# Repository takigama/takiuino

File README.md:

# Takiuino - the arduino compatible board for ME!

Just a WIP atm, look in the eagle directory and you can see the boards and their OSHPark links, though v2.0 has now
been tested against both arduino v1.0.x and arduino v1.5.7 and v1.6.0.

The main site for the takiuino is here: http://pjr.cc/tu/ (which is comming soon)

## Thanks go to....

Maniacbug - for his work on the 1284 originally, from [here](https://maniacbug.wordpress.com/2011/11/27/arduino-on-atmega1284p-4/).

The Optiboot folk - for making the awesome optiboot code! Available [here](https://code.google.com/p/optiboot/).

## What is it?

A fork of Maniacbug's mighty1284 code base, also includes the 644p code.

I've removed everything except the optiboot options (for now)

## What do you need?

First you need the board, which is on oshpark [here](https://oshpark.com/shared_projects/BunCIt50) for V3.1 or
[here](https://oshpark.com/shared_projects/wfCfnxof) for V3.2. The only difference between them is how the ICSP and reset swtiches are layed out.

# V3.1

# V3.2

Then you need to make the board (its pretty simple)

1. decide what you need, if your powering from a stable 5v source, you dont need the 5v REG (though keeping the 5v cap, C1, isnt a bad idea)
If you dont need a 3.3v line, you can drop the 3.3v REG as well (and its capacitor, C2).

2. the polarized components (2 caps, 2 leds) have their positive lines marked

3. Conquer the world. They'll be a better written tutorial coming soon, as well as an annotated
image of the actual board and components that go on it. But for the impatient the components are as follows:

- C1, C2: 10uf Tant CAP (16v rated)
- RES: SMD resontator (16mhz), Murata CSTCE16M0V53-R0 is appropriate
- C4: 0.1uf (100nf) 0603 sized ceramic cap
- R1: 330 ohm 0603 sized resister
- R2: 220 ohm 0603 sized resister (can also be 330 ohm if you wish)
- S1: SMD push button switch
- L2, L3: 0603 sized SMD led (note polarity)
- 1117-5v: AMS/LM1117 5v regulator
- 1117-3.3v: AMS/LM1117 3.3v regulator
- ATmega: ATmega1284p-au or ATmega644p-au (which ever suits you) should be a little circle on the chip, which 
goes with the printed circle on the board

Personally i find the resonator the hardest bit to solder, but doesnt take too much to long to get the hang
of it. After that, hook up an ASP and go program it directly with code, or use a bootloader and program via
the serial pinouts (note you'll need a USB to uart thingo).

If it all works, L3 should come on when power to the board is applied and you can control L2 via pummelling
pin 23 (which is what L2 is connected to). The following code should work:

```
int ledPin = 23;                 // LED connected to digital pin 23
float tLat = 1024;
bool dirUp = true;

void setup()
{
  Serial.begin(115200);
  pinMode(ledPin, OUTPUT);      // sets the digital pin as output
}

void loop()
{

  digitalWrite(ledPin, HIGH);   // sets the LED on
  delay(tLat);                  // waits for a bit
  digitalWrite(LED, LOW);       // sets the LED off
  // note that i use "LED" above, which is defined
  // in the hardware library for this pin
  delay(tLat);                  // waits for a bit

  if(tLat > 1024) {
    Serial.println("Switch direction, down");
    dirUp = false;

  }

  if(tLat < 2) {
    Serial.println("Switch direction, up");
    dirUp = true;
  }

  if(dirUp) {
    tLat = tLat*1.2;
  } else {
    tLat = tLat/1.2;
  }

  Serial.print("tlat now: ");
  Serial.println(tLat);

}

```
This should cause the L2 led to start as a slow on/off then ramp up and eventually stay on, then reset and start again.

## Installation

copy the contents of the arduino-ide folder into you arduino ide's hardware directory

## Why?

Originally started as a project to create something very specific, hence why the original V1 board has a
MOSFET on the board.

Second reason was cause I could, always wanted to design my own board for a microctronoller and this worked
out well.

Third was that I wanted a board with more useful pinout info, not many of the smaller boards have any markings
to tell you which channel is a pwm line, etc. The code also allow you to call pins via the names on
either side of the board (hence whey they're both there).

Lastly, I needed something small (round the pro mini/micro size) with two serial ports, the ability to run
an OLED screen (which requires quite some memory) along with some other memory sapping parts

## TODO

- I think I may regret the position of the reset switch as its sitting very close to the resonator (i'll know once
the v3 prints arrive from OSH Park)
- Write a test harness and some programs to check that the pins all work

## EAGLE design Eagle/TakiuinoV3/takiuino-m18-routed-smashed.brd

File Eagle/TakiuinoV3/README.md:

# Takuino V3 - the final countdown

Not quite here yet cause im a bit lazy sometimes.

Basically takiuino V3 will be V2 + silk screens on both sides with pin layouts
ISCP Header holes
Reset Button pads

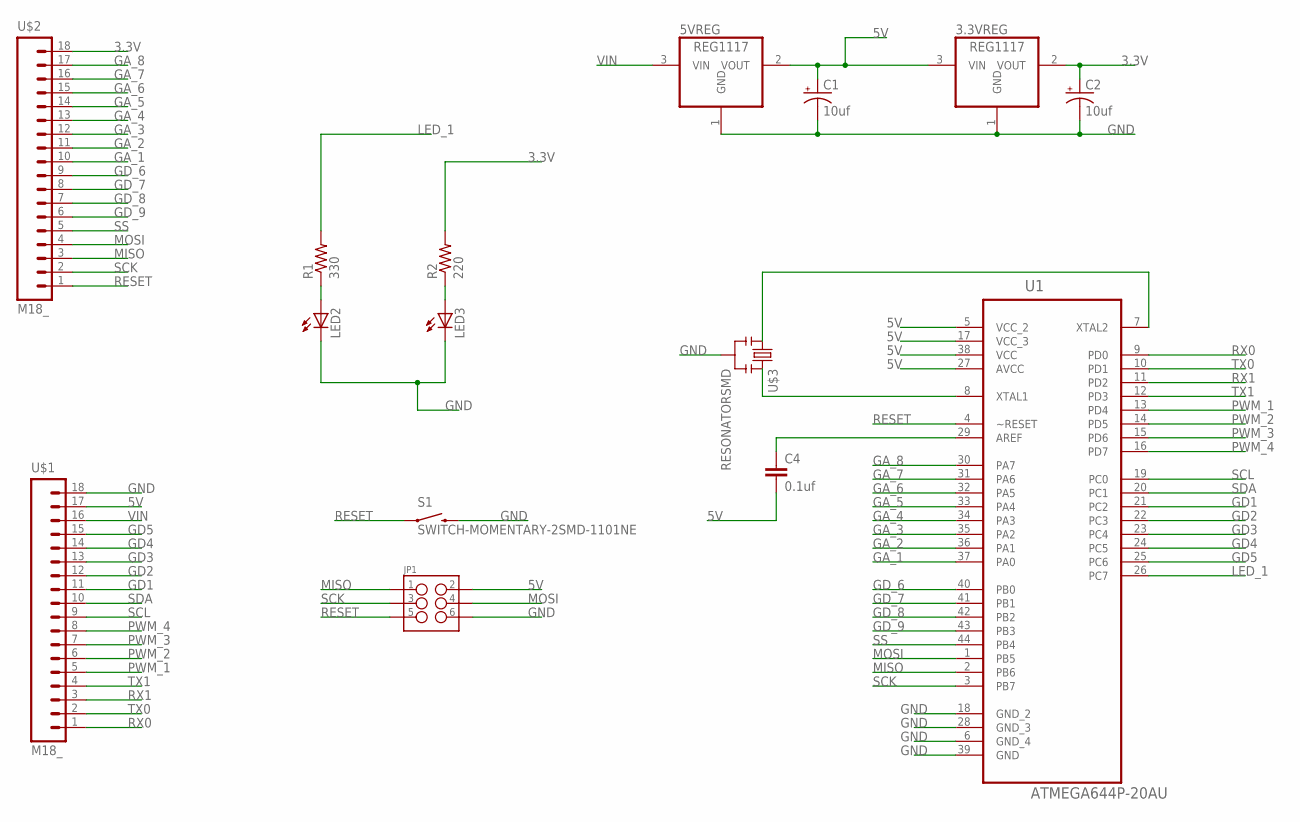
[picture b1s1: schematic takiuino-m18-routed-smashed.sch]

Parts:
3.3VREG, 5VREG: REG1117; SOT223
C1, C2: 10uf; EIA3216
C4: 0.1uf; 0603-CAP
JP1: M03X2NO_SILK; 2X3-NS
LED2, LED3: LEDCHIP-LED0603; CHIP-LED0603
R1: 330; R0603
R2: 220; R0603
S1: SWITCH-MOMENTARY-2SMD-1101NE; TACTILE-SWITCH-1101NE
U1: ATMEGA644P-20AU; QFP80P1200X1200X120-44N
U$1, U$2: M18_; 1X18
U$3: RESONATORSMD; RESONATOR-SMD

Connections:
3.3V: 3.3VREG.2 (VOUT), C2.A (+), R2.2, U$2.18
5V: 3.3VREG.3 (VIN), 5VREG.2 (VOUT), C1.A (+), C4.2, JP1.2, U1.5 (VCC_2), U1.17 (VCC_3), U1.27 (AVCC), U1.38 (VCC), U$1.17
GA_1: U1.37 (PA0), U$2.10
GA_2: U1.36 (PA1), U$2.11
GA_3: U1.35 (PA2), U$2.12
GA_4: U1.34 (PA3), U$2.13
GA_5: U1.33 (PA4), U$2.14
GA_6: U1.32 (PA5), U$2.15
GA_7: U1.31 (PA6), U$2.16
GA_8: U1.30 (PA7), U$2.17
GD1: U1.21 (PC2), U$1.11
GD2: U1.22 (PC3), U$1.12
GD3: U1.23 (PC4), U$1.13
GD4: U1.24 (PC5), U$1.14
GD5: U1.25 (PC6), U$1.15
GD_6: U1.40 (PB0), U$2.9
GD_7: U1.41 (PB1), U$2.8
GD_8: U1.42 (PB2), U$2.7
GD_9: U1.43 (PB3), U$2.6
GND: 3.3VREG.1 (GND), 5VREG.1 (GND), C1.C (-), C2.C (-), JP1.6, LED2.C, LED3.C, S1.2, U1.6 (GND_4), U1.18 (GND_2), U1.28 (GND_3), U1.39 (GND), U$1.18, U$3.2
LED_1: R1.2, U1.26 (PC7)
MISO: JP1.1, U1.2 (PB6), U$2.3
MOSI: JP1.4, U1.1 (PB5), U$2.4
unnamed: U1.8 (XTAL1), U$3.3
unnamed: U1.7 (XTAL2), U$3.1
unnamed: C4.1, U1.29 (AREF)
unnamed: LED2.A, R1.1
unnamed: LED3.A, R2.1
PWM_1: U1.13 (PD4), U$1.5
PWM_2: U1.14 (PD5), U$1.6
PWM_3: U1.15 (PD6), U$1.7
PWM_4: U1.16 (PD7), U$1.8
RESET: JP1.5, S1.1, U1.4 (~RESET), U$2.1
RX0: U1.9 (PD0), U$1.1
RX1: U1.11 (PD2), U$1.3
SCK: JP1.3, U1.3 (PB7), U$2.2
SCL: U1.19 (PC0), U$1.9
SDA: U1.20 (PC1), U$1.10
SS: U1.44 (PB4), U$2.5
TX0: U1.10 (PD1), U$1.2
TX1: U1.12 (PD3), U$1.4
VIN: 5VREG.3 (VIN), U$1.16

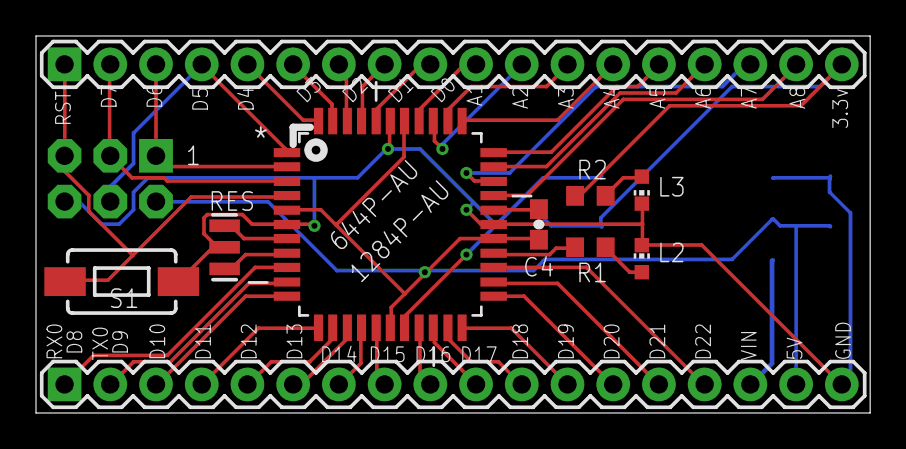
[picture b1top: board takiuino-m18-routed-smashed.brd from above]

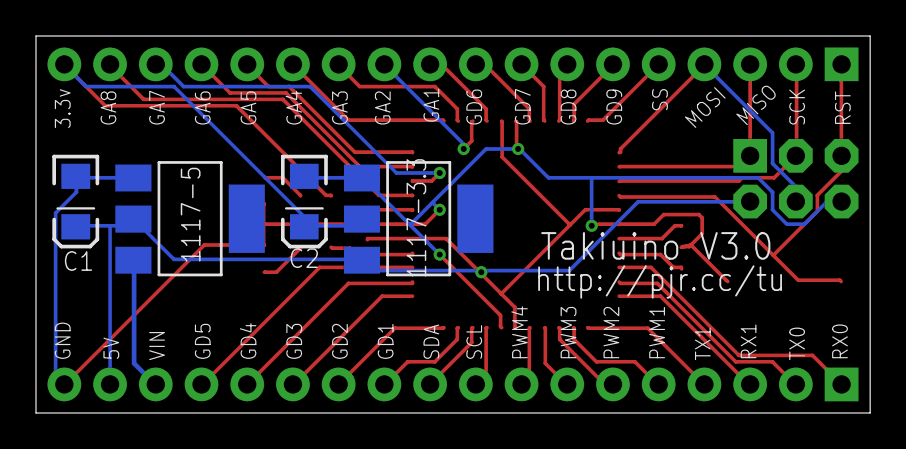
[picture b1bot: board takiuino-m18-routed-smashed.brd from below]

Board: 2 copper layers, 46.3 x 20.9 mm, 15 parts (4 on the bottom side), 42 nets.

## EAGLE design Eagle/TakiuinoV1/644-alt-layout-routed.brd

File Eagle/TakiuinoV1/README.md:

# Takiuino V1

This board had a very specific purpose and should never actually be built, unless you very much want a board with an inbuilt MOSFET connector.

I've included the gerber files, or alternatively it can be printed on oshpark https://oshpark.com/shared_projects/UIUpYUVF

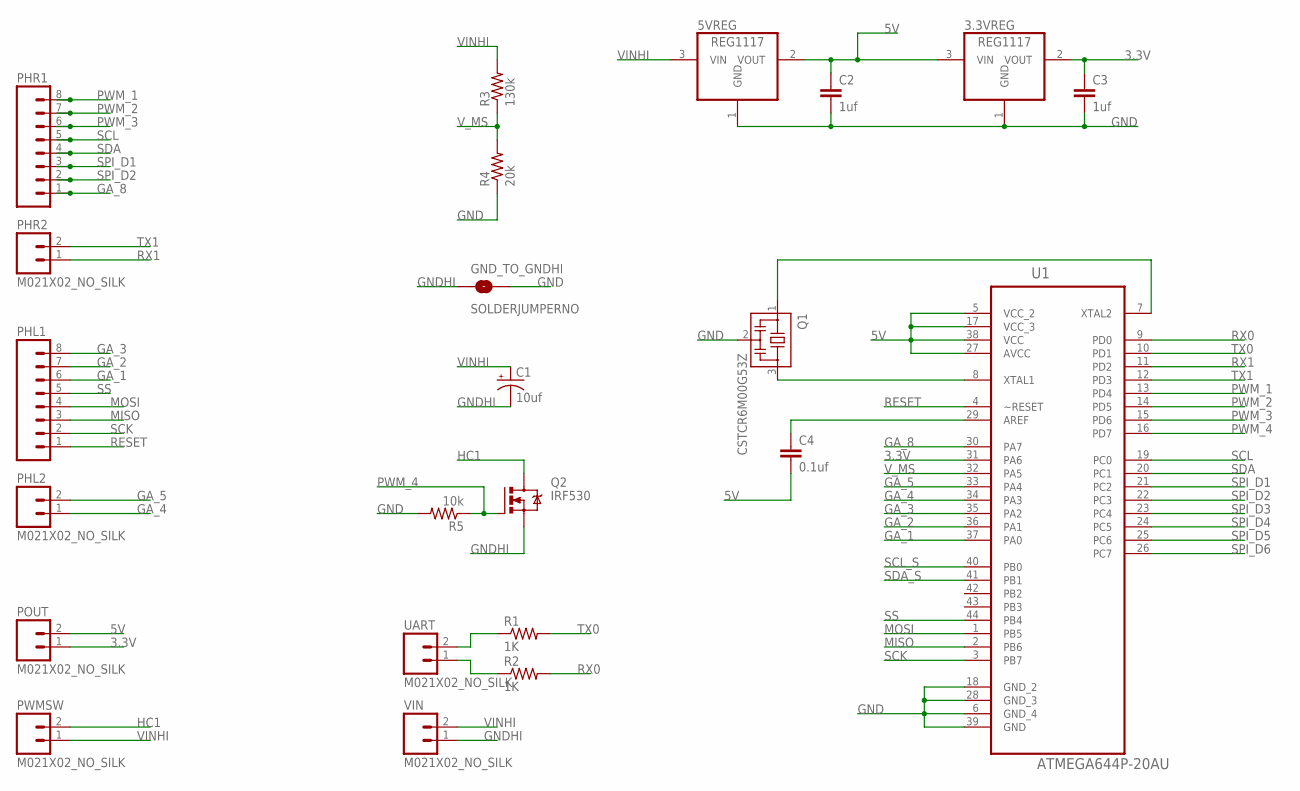
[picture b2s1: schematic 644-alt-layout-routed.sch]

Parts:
3.3VREG, 5VREG: REG1117; SOT223
C1: 10uf; EIA3216
C2, C3: 1uf; 0603-CAP
C4: 0.1uf; 0603-CAP
GND_TO_GNDHI: SOLDERJUMPERNO; SJ_2S-NO
PHL1: M08NO_SILK; 1X08_PIN1_NO_SILK
PHL2: M021X02_NO_SILK; 1X02_NO_SILK
PHR1: M08NO_SILK; 1X08_PIN1_NO_SILK
PHR2: M021X02_NO_SILK; 1X02_NO_SILK
POUT: M021X02_NO_SILK; 1X02_NO_SILK
PWMSW: M021X02_NO_SILK; 1X02_NO_SILK
Q1: CSTCR6M00G53Z; CSTCR6M
Q2: IRF530; TO220BV
R1, R2: 1K; 0603-RES
R3: 130k; 0603-RES
R4: 20k; 0603-RES
R5: 10k; 0603-RES
U1: ATMEGA644P-20AU; QFP80P1200X1200X120-44N
UART: M021X02_NO_SILK; 1X02_NO_SILK
VIN: M021X02_NO_SILK; 1X02_NO_SILK

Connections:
3.3V: 3.3VREG.2 (VOUT), C3.1, POUT.1, U1.31 (PA6)
5V: 3.3VREG.3 (VIN), 5VREG.2 (VOUT), C2.1, C4.2, POUT.2, U1.5 (VCC_2), U1.17 (VCC_3), U1.27 (AVCC), U1.38 (VCC)
GA_1: PHL1.6, U1.37 (PA0)
GA_2: PHL1.7, U1.36 (PA1)
GA_3: PHL1.8, U1.35 (PA2)
GA_4: PHL2.1, U1.34 (PA3)
GA_5: PHL2.2, U1.33 (PA4)
GA_8: PHR1.1, U1.30 (PA7)
GND: 3.3VREG.1 (GND), 5VREG.1 (GND), C2.2, C3.2, GND_TO_GNDHI.2, Q1.2, R4.1, R5.2, U1.6 (GND_4), U1.18 (GND_2), U1.28 (GND_3), U1.39 (GND)
GNDHI: C1.C (-), GND_TO_GNDHI.1, Q2.S, VIN.1
HC1: PWMSW.2, Q2.D
MISO: PHL1.3, U1.2 (PB6)
MOSI: PHL1.4, U1.1 (PB5)
unnamed: Q1.3, U1.8 (XTAL1)
unnamed: Q1.1, U1.7 (XTAL2)
unnamed: C4.1, U1.29 (AREF)
unnamed: R1.1, UART.2
unnamed: R2.1, UART.1
PWM_1: PHR1.8, U1.13 (PD4)
PWM_2: PHR1.7, U1.14 (PD5)
PWM_3: PHR1.6, U1.15 (PD6)
PWM_4: Q2.G, R5.1, U1.16 (PD7)
RESET: PHL1.1, U1.4 (~RESET)
RX0: R2.2, U1.9 (PD0)
RX1: PHR2.1, U1.11 (PD2)
SCK: PHL1.2, U1.3 (PB7)
SCL: PHR1.5, U1.19 (PC0)
SCL_S: U1.40 (PB0)
SDA: PHR1.4, U1.20 (PC1)
SDA_S: U1.41 (PB1)
SPI_D1: PHR1.3, U1.21 (PC2)
SPI_D2: PHR1.2, U1.22 (PC3)
SPI_D3: U1.23 (PC4)
SPI_D4: U1.24 (PC5)
SPI_D5: U1.25 (PC6)
SPI_D6: U1.26 (PC7)
SS: PHL1.5, U1.44 (PB4)
TX0: R1.2, U1.10 (PD1)
TX1: PHR2.2, U1.12 (PD3)
VINHI: 5VREG.3 (VIN), C1.A (+), PWMSW.1, R3.2, VIN.2
V_MS: R3.1, R4.2, U1.32 (PA5)

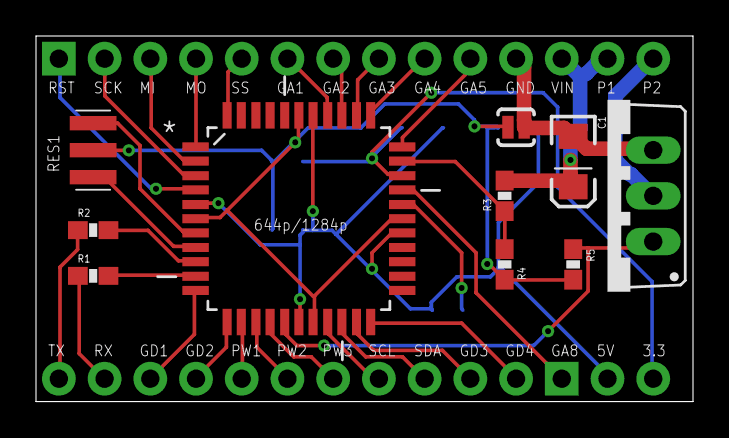
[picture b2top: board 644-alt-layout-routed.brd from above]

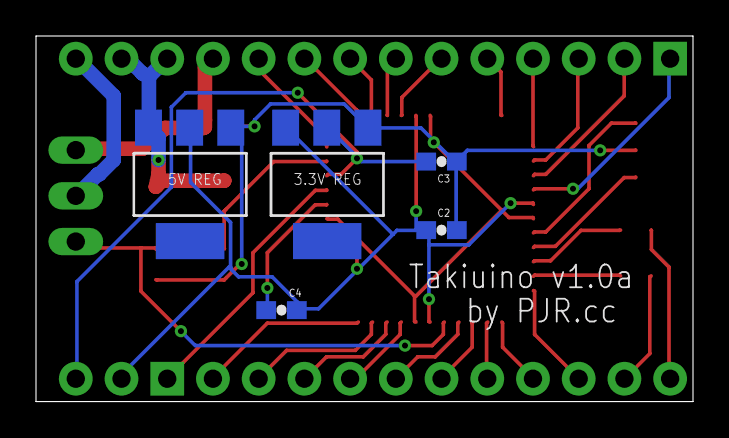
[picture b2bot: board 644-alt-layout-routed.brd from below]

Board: 2 copper layers, 36.5 x 20.3 mm, 23 parts (5 on the bottom side), 35 nets.

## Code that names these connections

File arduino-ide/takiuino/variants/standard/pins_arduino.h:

#ifndef Pins_Arduino_h
#define Pins_Arduino_h

#include <avr/pgmspace.h>

// ATMEL ATMEGA1284P
//
//                   +---\/---+
//           (D 0) PB0  1|        |40  PA0 (AI 0 / D24)
//           (D 1) PB1  2|        |39  PA1 (AI 1 / D25)
//      INT2 (D 2) PB2  3|        |38  PA2 (AI 2 / D26)
//       PWM (D 3) PB3  4|        |37  PA3 (AI 3 / D27)
//    PWM/SS (D 4) PB4  5|        |36  PA4 (AI 4 / D28)
//      MOSI (D 5) PB5  6|        |35  PA5 (AI 5 / D29)
//  PWM/MISO (D 6) PB6  7|        |34  PA6 (AI 6 / D30)
//   PWM/SCK (D 7) PB7  8|        |33  PA7 (AI 7 / D31)
//                 RST  9|        |32  AREF
//                 VCC 10|        |31  GND 
//                 GND 11|        |30  AVCC
//               XTAL2 12|        |29  PC7 (D 23)
//               XTAL1 13|        |28  PC6 (D 22)
//      RX0 (D 8)  PD0 14|        |27  PC5 (D 21) TDI
//      TX0 (D 9)  PD1 15|        |26  PC4 (D 20) TDO
// RX1/INT0 (D 10) PD2 16|        |25  PC3 (D 19) TMS
// TX1/INT1 (D 11) PD3 17|        |24  PC2 (D 18) TCK
//      PWM (D 12) PD4 18|        |23  PC1 (D 17) SDA
//      PWM (D 13) PD5 19|        |22  PC0 (D 16) SCL
//      PWM (D 14) PD6 20|        |21  PD7 (D 15) PWM
//                   +--------+
//

/*
   PCINT15-8: D7-0  : bit 1
   PCINT31-24: D15-8  : bit 3
   PCINT23-16: D23-16 : bit 2
   PCINT7-0: D31-24   : bit 0
   */

#define NUM_DIGITAL_PINS            31
#define NUM_ANALOG_INPUTS           8
#define analogInputToDigitalPin(p)  ((p < NUM_ANALOG_INPUTS) ? (p) + 24 : -1)

#define digitalPinHasPWM(p)         ((p) == 3 || (p) == 4 || (p) == 6 || (p) == 7 || (p) == 12 || (p) == 13 || (p) == 14 || (p) == 15)


// backside pin def's
static const uint8_t PWM1 = 12;
static const uint8_t PWM2 = 13;
static const uint8_t PWM3 = 14;
static const uint8_t PWM4 = 15;

// second serial port
static const uint8_t RX1 = 10;
static const uint8_t TX1 = 11;

// on board led which i didnt bring to a pin
static const uint8_t LED = 23;
static const uint8_t LED1 = 23;

// general analog ports
static const uint8_t GA1 = 24;
static const uint8_t GA2 = 25;
static const uint8_t GA3 = 26;
static const uint8_t GA4 = 27;
static const uint8_t GA5 = 28;
static const uint8_t GA6 = 29;
static const uint8_t GA7 = 30;
static const uint8_t GA8 = 31;

// general digital ports
static const uint8_t GD1 = 18;
static const uint8_t GD2 = 19;
static const uint8_t GD3 = 20;
static const uint8_t GD4 = 21;
static const uint8_t GD5 = 22;
static const uint8_t GD6 = 0;
static const uint8_t GD7 = 1;
static const uint8_t GD8 = 2;
static const uint8_t GD9 = 3;

// end backside pin defs


static const uint8_t SS   = 4;
static const uint8_t MOSI = 5;
static const uint8_t MISO = 6;
static const uint8_t SCK  = 7;

static const uint8_t SDA = 17;
static const uint8_t SCL = 16;

static const uint8_t A0 = 24;
static const uint8_t A1 = 25;
static const uint8_t A2 = 26;
static const uint8_t A3 = 27;
static const uint8_t A4 = 28;
static const uint8_t A5 = 29;
static const uint8_t A6 = 30;
static const uint8_t A7 = 31;

#define digitalPinToPCICR(p)    (((p) >= 0 && (p) < NUM_DIGITAL_PINS) ? (&PCICR) : ((uint8_t *)0))
#define digitalPinToPCICRbit(p) (((p) <= 7) ? 1 : (((p) <= 15) ? 3 : (((p) <= 23) ? 2 : 0)))
#define digitalPinToPCMSK(p)    (((p) <= 7) ? (&PCMSK2) : (((p) <= 13) ? (&PCMSK0) : (((p) <= 21) ? (&PCMSK1) : ((uint8_t *)0))))
#define digitalPinToPCMSKbit(p) ((p) % 8)

#ifdef ARDUINO_MAIN

#define PA 1
#define PB 2
#define PC 3
#define PD 4

// these arrays map port names (e.g. port B) to the
// appropriate addresses for various functions (e.g. reading
// and writing)
const uint16_t PROGMEM port_to_mode_PGM[] =
{
	NOT_A_PORT,
	(uint16_t) &DDRA,
	(uint16_t) &DDRB,
	(uint16_t) &DDRC,
	(uint16_t) &DDRD,
};

const uint16_t PROGMEM port_to_output_PGM[] =
{
	NOT_A_PORT,
	(uint16_t) &PORTA,
	(uint16_t) &PORTB,
	(uint16_t) &PORTC,
	(uint16_t) &PORTD,
};

const uint16_t PROGMEM port_to_input_PGM[] =
{
	NOT_A_PORT,
	(uint16_t) &PINA,
	(uint16_t) &PINB,
	(uint16_t) &PINC,
	(uint16_t) &PIND,
};

const uint8_t PROGMEM digital_pin_to_port_PGM[] =
{
	PB, /* 0 */
	PB,
	PB,
	PB,
	PB,
	PB,
	PB,
	PB,
	PD, /* 8 */
	PD,
	PD,
	PD,
	PD,
	PD,
	PD,
	PD,
	PC, /* 16 */
	PC,
	PC,
	PC,
	PC,
	PC,
   	PC,
	PC,
	PA, /* 24 */
	PA,
	PA,
	PA,
	PA,
	PA,
	PA,
	PA  /* 31 */
};

const uint8_t PROGMEM digital_pin_to_bit_mask_PGM[] =
{
	_BV(0), /* 0, port B */
	_BV(1),
	_BV(2),
	_BV(3),
	_BV(4),
	_BV(5),
	_BV(6),
	_BV(7),
	_BV(0), /* 8, port D */
	_BV(1),
	_BV(2),
	_BV(3),
	_BV(4),
	_BV(5),
	_BV(6),
	_BV(7),
	_BV(0), /* 16, port C */
	_BV(1),
	_BV(2),
	_BV(3),
	_BV(4),
	_BV(5),
	_BV(6),
	_BV(7),
	_BV(0), /* 24, port A */
	_BV(1),
	_BV(2),
	_BV(3),
	_BV(4),
	_BV(5),
	_BV(6),
	_BV(7)
};

const uint8_t PROGMEM digital_pin_to_timer_PGM[] =
{
	NOT_ON_TIMER, 	/* 0  - PB0 */
	NOT_ON_TIMER, 	/* 1  - PB1 */
	NOT_ON_TIMER, 	/* 2  - PB2 */
	TIMER0A,     	/* 3  - PB3 */
	TIMER0B, 	/* 4  - PB4 */
	NOT_ON_TIMER, 	/* 5  - PB5 */
	TIMER3A, 	/* 6  - PB6 */
	TIMER3B,	/* 7  - PB7 */
	NOT_ON_TIMER, 	/* 8  - PD0 */
	NOT_ON_TIMER, 	/* 9  - PD1 */
	NOT_ON_TIMER, 	/* 10 - PD2 */
	NOT_ON_TIMER, 	/* 11 - PD3 */
	TIMER1B,     	/* 12 - PD4 */
	TIMER1A,     	/* 13 - PD5 */
	TIMER2B,     	/* 14 - PD6 */
	TIMER2A,     	/* 15 - PD7 */
	NOT_ON_TIMER, 	/* 16 - PC0 */
	NOT_ON_TIMER,   /* 17 - PC1 */
	NOT_ON_TIMER,   /* 18 - PC2 */
	NOT_ON_TIMER,   /* 19 - PC3 */
	NOT_ON_TIMER,   /* 20 - PC4 */
	NOT_ON_TIMER,   /* 21 - PC5 */
	NOT_ON_TIMER,   /* 22 - PC6 */
	NOT_ON_TIMER,   /* 23 - PC7 */
	NOT_ON_TIMER,   /* 24 - PA0 */
	NOT_ON_TIMER,   /* 25 - PA1 */
	NOT_ON_TIMER,   /* 26 - PA2 */
	NOT_ON_TIMER,   /* 27 - PA3 */
	NOT_ON_TIMER,   /* 28 - PA4 */
	NOT_ON_TIMER,   /* 29 - PA5 */
	NOT_ON_TIMER,   /* 30 - PA6 */
	NOT_ON_TIMER   /* 31 - PA7 */
};

#endif // ARDUINO_MAIN

#endif // Pins_Arduino_h
// vim:ai:cin:sts=2 sw=2 ft=cpp

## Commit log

2015-03-01 initial project drop into github
2015-03-01 added some small comments to readme
2015-03-05 Takuino V3 eagle files
2015-03-06 Updates for the takiuino v3.1 board - pin number fixed and positive terminals marked on polarised componets
2015-03-06 updated for small layout fixes, make markings a little easier to read
2015-03-06 ocd kicked in and one of the lines was slightly out - was driving me nuts - updated
2015-03-06 OCD related problem
2015-03-07 updated some info
2015-03-07 updated some build info
2015-03-07 updated with some build info
2015-03-07 pin definitions for backside port names (on the silk screen) defined
2015-03-07 including the oshpark renders
2015-03-07 minor textual updates to the readme
2015-03-07 beginnings of test code
2015-03-07 test source code
2015-03-08 changes for arduino 1.5
2015-03-08 tested and working with arduino 1.0 and 1.5/1.6
2015-03-08 slight change to the way the accelarating led code works (now bounces)
2015-03-08 clean up the source and readme
2015-03-08 rename directory
2015-03-08 Update for v3.2 with moved ICSP and switch
2015-03-08 just little text updates
2015-05-26 forgot a tooling line
2015-05-26 boot block path

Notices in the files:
parts and their libraries:
SparkFun-Capacitors: Licensing: Creative Commons ShareAlike 4.0 International - https://creativecommons.org/licenses/by-sa/4.0
